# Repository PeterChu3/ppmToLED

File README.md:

# ppmToLED
## Story

I ride with my friend Brendan Bassett on our electric skateboards around Atlanta. However, there is a slight problem with Brendan's build. Under high speed the board seems to cutout with no fault recorded. We are assuming that the motor controller is fine and Brendan's hand controller/reciever is briefly not outputing the correct ppm signal. We had issues with the remote before, but we had to design and make our solution to test our theory. 

## Our solution
We will tap into the PPM signal and decode it using a microcontroller. 

Then we will output to some addressable LEDs. We will code a map function that intensifies the brightness based on the magnitude of the PPM signal. 

Full brake would result in full brightness red.

Full acceleration would result in full brightness green.

A neutral signal would result in off LEDs or display a neutral color.

## Explanation
The board uses a ATtiny85 to decode the PPM signal and output to a few addressable LEDs.

We chose the ATtiny85 because of it's simplicty and compact package. Also, Georgia Tech's makerspace provides them for free.

The input is 5v and provided by the motor controller.

The outputs are also 5v on all connectors. There is a connector for both PPM and LED out.

## Pinout

Pin 2 is an input pin for the PPM signal. 

Pin 4 is an OUTPUT pin for the address LEDs. 
Library to drive Pin 4 TBD.

## Schematic and Board layout

Schematic view

Layout view

Board view

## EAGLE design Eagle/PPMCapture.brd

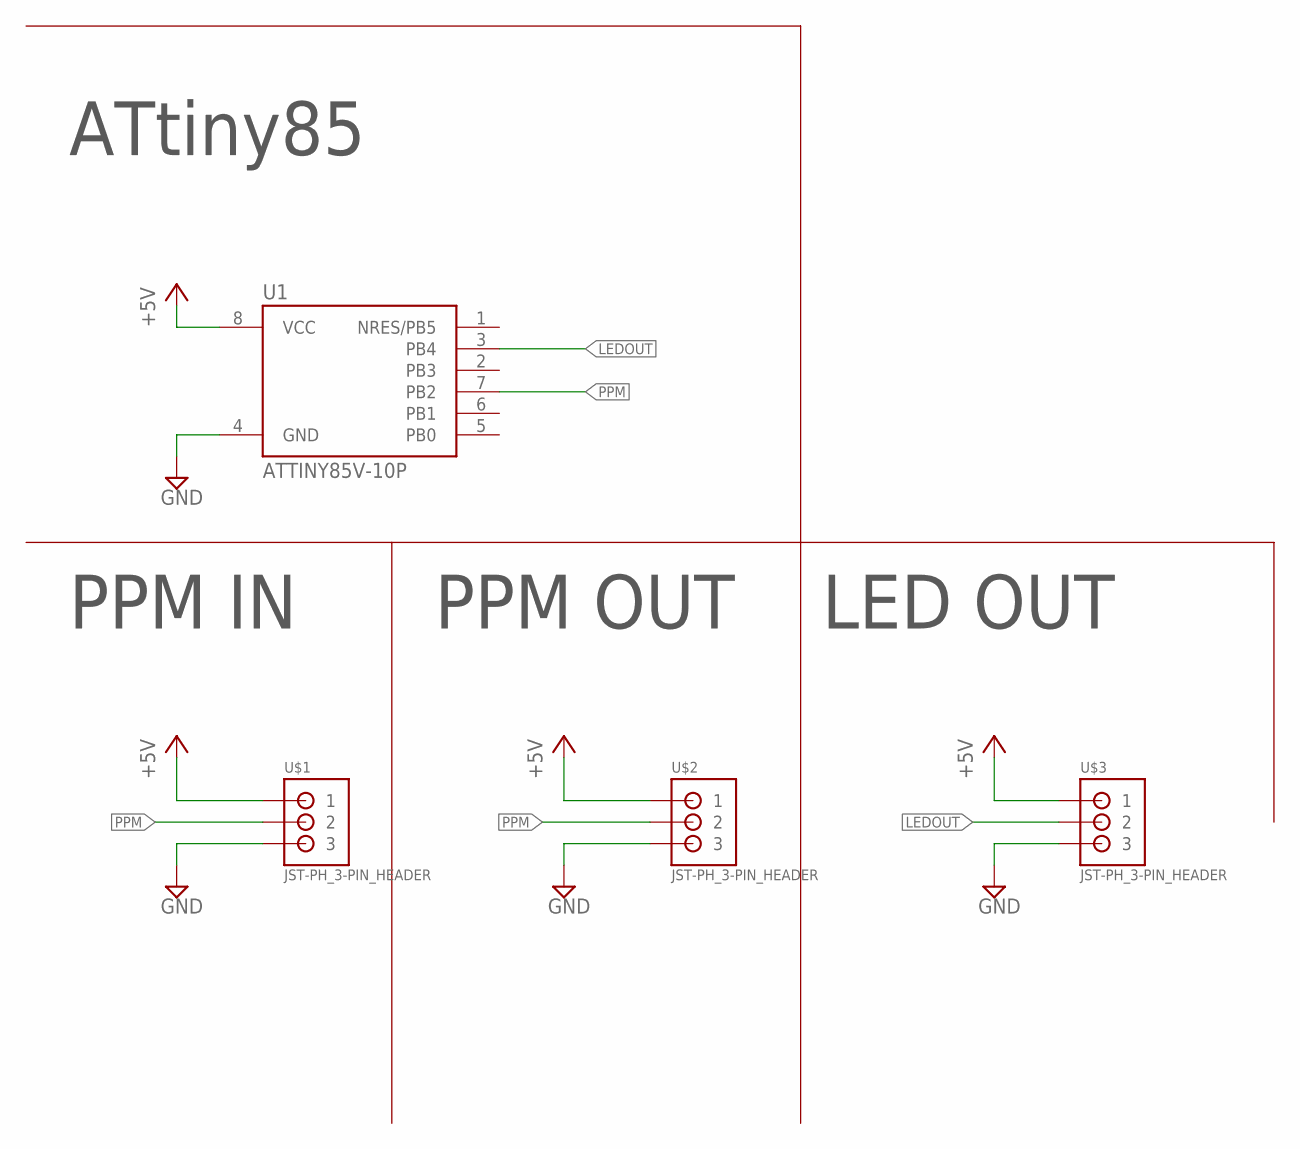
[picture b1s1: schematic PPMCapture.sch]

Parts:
U1: ATTINY85V-10P; PDIP08_300MIL
U$1, U$2, U$3: JST-PH_3-PIN_HEADER; JST_B3B-PH_HEADER

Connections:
+5V: U1.8 (VCC), U$1.P1 (1), U$2.P1 (1), U$3.P1 (1)
GND: U1.4 (GND), U$1.P3 (3), U$2.P3 (3), U$3.P3 (3)
LEDOUT: U1.3 (PB4), U$3.P2 (2)
PPM: U1.7 (PB2), U$1.P2 (2), U$2.P2 (2)

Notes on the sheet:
PPM IN
PPM OUT
LED OUT
ATtiny85

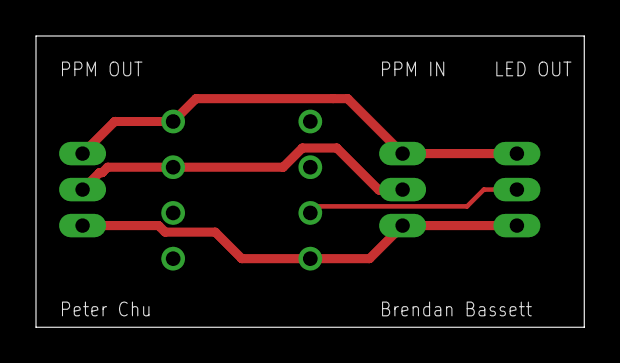
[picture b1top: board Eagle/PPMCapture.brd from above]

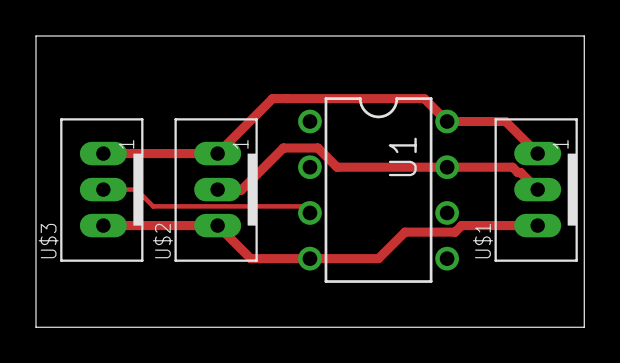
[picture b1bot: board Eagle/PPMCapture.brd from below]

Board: 2 copper layers, 30.5 x 16.2 mm, 4 parts (4 on the bottom side), 4 nets.

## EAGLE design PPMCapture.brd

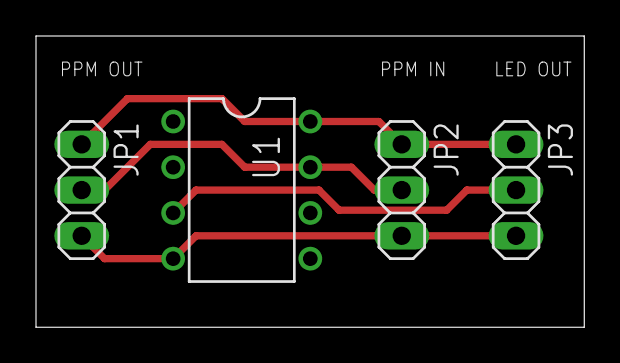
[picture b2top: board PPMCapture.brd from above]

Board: 2 copper layers, 30.5 x 16.2 mm, 4 parts (0 on the bottom side), 4 nets.

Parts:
JP1, JP2, JP3: 1X03
U1: ATTINY85V-10P; PDIP08_300MIL

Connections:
+5V: JP1.1, JP2.1, JP3.1, U1.8
GND: JP1.3, JP2.3, JP3.3, U1.4
LEDOUT: JP3.2, U1.3
PPM: JP1.2, JP2.2, U1.7

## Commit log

2022-02-11 added gitignore
2022-02-11 Added schematic and Board
2022-02-11 .DS_Store banished!
2022-02-11 Reorganized files
2022-02-11 Added riding gif
2022-02-11 added board and schematic images
2022-02-11 added more images
2022-02-11 Added Readme
2022-02-11 Chaned .1 header to JST 3pin connector
2022-02-11 Flipped board for PCB milling
